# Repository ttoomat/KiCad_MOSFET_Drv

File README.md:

# Плата драйвера  MOSFET

В этой репозитории я храню печатные платы. Здесь есть одиночная печатная плата драйвера с мосфетом, будет добавлена плата полумоста на ключах
переменного тока. И общая плата, состоящая из полумостов.

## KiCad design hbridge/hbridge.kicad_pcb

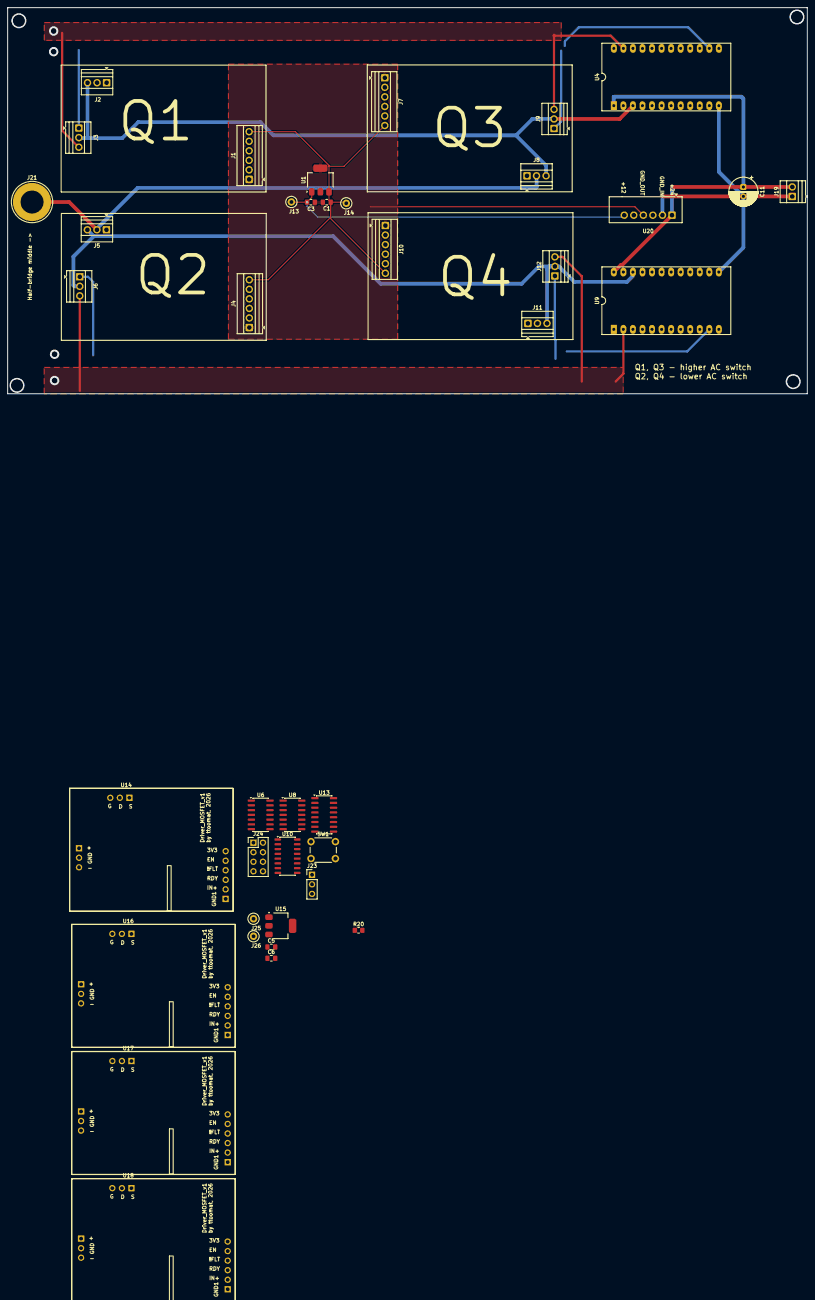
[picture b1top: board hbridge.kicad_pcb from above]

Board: 2 copper layers, 212.8 x 102.7 mm, 40 parts (0 on the bottom side), 41 nets.

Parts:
C1, C3: C; C_0805_2012Metric_Pad1.18x1.45mm_HandSolder
C5: 10u; C_0805_2012Metric_Pad1.18x1.45mm_HandSolder
C6: 2.2u; C_0805_2012Metric_Pad1.18x1.45mm_HandSolder
C11: 100-220uF/50V; CP_Radial_D7.5mm_P2.50mm
J1, J4, J7, J10: From_MCU; TerminalBlock_Xinya_XY308-2.54-6P_1x06_P2.54mm_Horizontal
J2, J5, J8, J11: MOSFET_out; TerminalBlock_Xinya_XY308-2.54-3P_1x03_P2.54mm_Horizontal
J3, J6, J9, J12: Conn_01x03; TerminalBlock_Xinya_XY308-2.54-3P_1x03_P2.54mm_Horizontal
J13, J14, J25, J26: Conn_01x01_Socket; TestPoint_Loop_D1.80mm_Drill1.0mm_Beaded
J19: 24V; TerminalBlock_Xinya_XY308-2.54-2P_1x02_P2.54mm_Horizontal
J21: Conn_01x01_Socket; Banana_Jack_1Pin
J23: Conn_01x03; PinHeader_1x03_P2.54mm_Vertical
J24: Conn_01x08_Pin; PinHeader_2x04_P2.54mm_Vertical
R20: 1k; R_0805_2012Metric_Pad1.20x1.40mm_HandSolder
SW1: SW_Push; SW_PUSH_6mm_H4.3mm
U1, U15: LDO-3.3; SOT-223-3_TabPin2
U4, U9: AM6TW-2415DZ; DIP-24_18.0mmx34.29mm_W15.24mm_LongPads
U6: MC74HC08ADG (74HC08); SOIC-14_3.9x8.7mm_P1.27mm
U8: 74AHC04; SOIC-14_3.9x8.7mm_P1.27mm
U10: 74HC165; SO-16_3.9x9.9mm_P1.27mm
U13: CD4043B; SOIC-16_3.9x9.9mm_P1.27mm
U14, U16, U17, U18: driver_MOSFET_board; плата драйвера
U20: B2412S-2WR3; TerminalBlock_Xinya_XY308-2.54-6P_1x06_P2.54mm_Horizontal

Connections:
+3V3_DRV1: C1.1, C5.1, J1.6, J4.6, J7.6, J10.6, J14.1 (Pin_1_1), J25.1 (Pin_1_1), SW1.2, U1.3 (OUT), U6.14 (VCC), U8.14 (VCC), U10.16 (VCC), U13.5 (EN), U13.16 (VDD), U14.6 (+3V3_VCC1), U15.3 (OUT), U16.6 (+3V3_VCC1), U17.6 (+3V3_VCC1), U18.6 (+3V3_VCC1)
+12V: C3.1, C6.1, J13.1 (Pin_1_1), J26.1 (Pin_1_1), U1.1 (IN), U15.1 (IN), U20.6 (+VOUT)
+15_DRV2_H: J3.1, J9.1, U4.14 (+VOUT), U14.10 (+15_VCC2), U17.10 (+15_VCC2)
+15_DRV2_L: J6.1, J12.1, U9.11 (+VOUT), U16.10 (+15_VCC2), U18.10 (+15_VCC2)
+24V_1: C11.1, J19.2, U4.1 (+VIN), U9.24 (+VIN), U20.1 (VIN)
-15_DRV2_H: J3.3, J9.3, U4.23 (-VOUT), U14.12 (-15_VEE2), U17.12 (-15_VEE2)
-15_DRV2_L: J6.3, J12.3, U9.2 (-VOUT), U16.12 (-15_VEE2), U18.12 (-15_VEE2)
/драйверы old/drain2: J5.2, J8.2, J21.1 (Pin_1_1)
EN1: J1.5, U13.2 (Q1), U14.5 (EN)
EN2: J4.5, U13.9 (Q2), U16.5 (EN)
EN3: J7.5, U13.10 (Q3), U17.5 (EN)
EN4: J10.5, U13.1 (Q4), U18.5 (EN)
ERR_CLK: J23.3, U10.2 (CP)
ERR_CS: J23.2, U10.1 (~PL)
ERR_SERIAL_DATA: J23.1, U10.9 (Q7)
FLT1: J1.4, J24.2, U6.2, U10.12 (D1), U14.4 (!FLT)
FLT2: J4.4, J24.4, U6.5, U10.14 (D3), U16.4 (!FLT)
FLT3: J7.4, J24.6, U6.10, U10.4 (D5), U17.4 (!FLT)
FLT4: J10.4, J24.8, U6.13, U10.6 (D7), U18.4 (!FLT)
GND1: C11.2, J19.1, U4.12 (-VIN), U9.13 (-VIN), U20.2 (GND_IN)
GND_DRV1: C1.2, C3.2, C5.2, C6.2, J1.1, J4.1, J7.1, J10.1, R20.2, U1.2 (GND), U6.7 (GND), U8.7 (GND), U10.8 (GND), U10.10 (DS), U10.15 (~CE), U13.8 (VSS(GND)), U14.1 (GND1), U15.2 (GND), U16.1 (GND1), U17.1 (GND1), U18.1 (GND1), U20.4 (GND_OUT)
GND_DRV2_H: J2.3, J3.2, J8.3, J9.2, U4.3 (COM), U14.9 (source), U14.11 (GND2), U17.9 (source), U17.11 (GND2)
GND_DRV2_L: J5.3, J6.2, J11.3, J12.2, U9.22 (COM), U16.9 (source), U16.11 (GND2), U18.9 (source), U18.11 (GND2)
IN1: J1.2, U14.2 (IN+)
IN2: J4.2, U16.2 (IN+)
IN3: J7.2, U17.2 (IN+)
IN4: J10.2, U18.2 (IN+)
unnamed: U6.3, U8.1
unnamed: U6.6, U8.3
unnamed: U6.8, U8.5
unnamed: U6.11, U8.9
unnamed: U8.2, U13.3 (R1)
unnamed: R20.1, SW1.1, U13.4 (S1), U13.6 (S2), U13.12 (S3), U13.14 (S4)
unnamed: U8.4, U13.7 (R2)
unnamed: U8.6, U13.11 (R3)
unnamed: U8.8, U13.15 (R4)
unnamed: U16.8 (drain), U17.8 (drain)
RDY1: J1.3, J24.1, U6.1, U10.11 (D0), U14.3 (RDY)
RDY2: J4.3, J24.3, U6.4, U10.13 (D2), U16.3 (RDY)
RDY3: J7.3, J24.5, U6.9, U10.3 (D4), U17.3 (RDY)
RDY4: J10.3, J24.7, U6.12, U10.5 (D6), U18.3 (RDY)

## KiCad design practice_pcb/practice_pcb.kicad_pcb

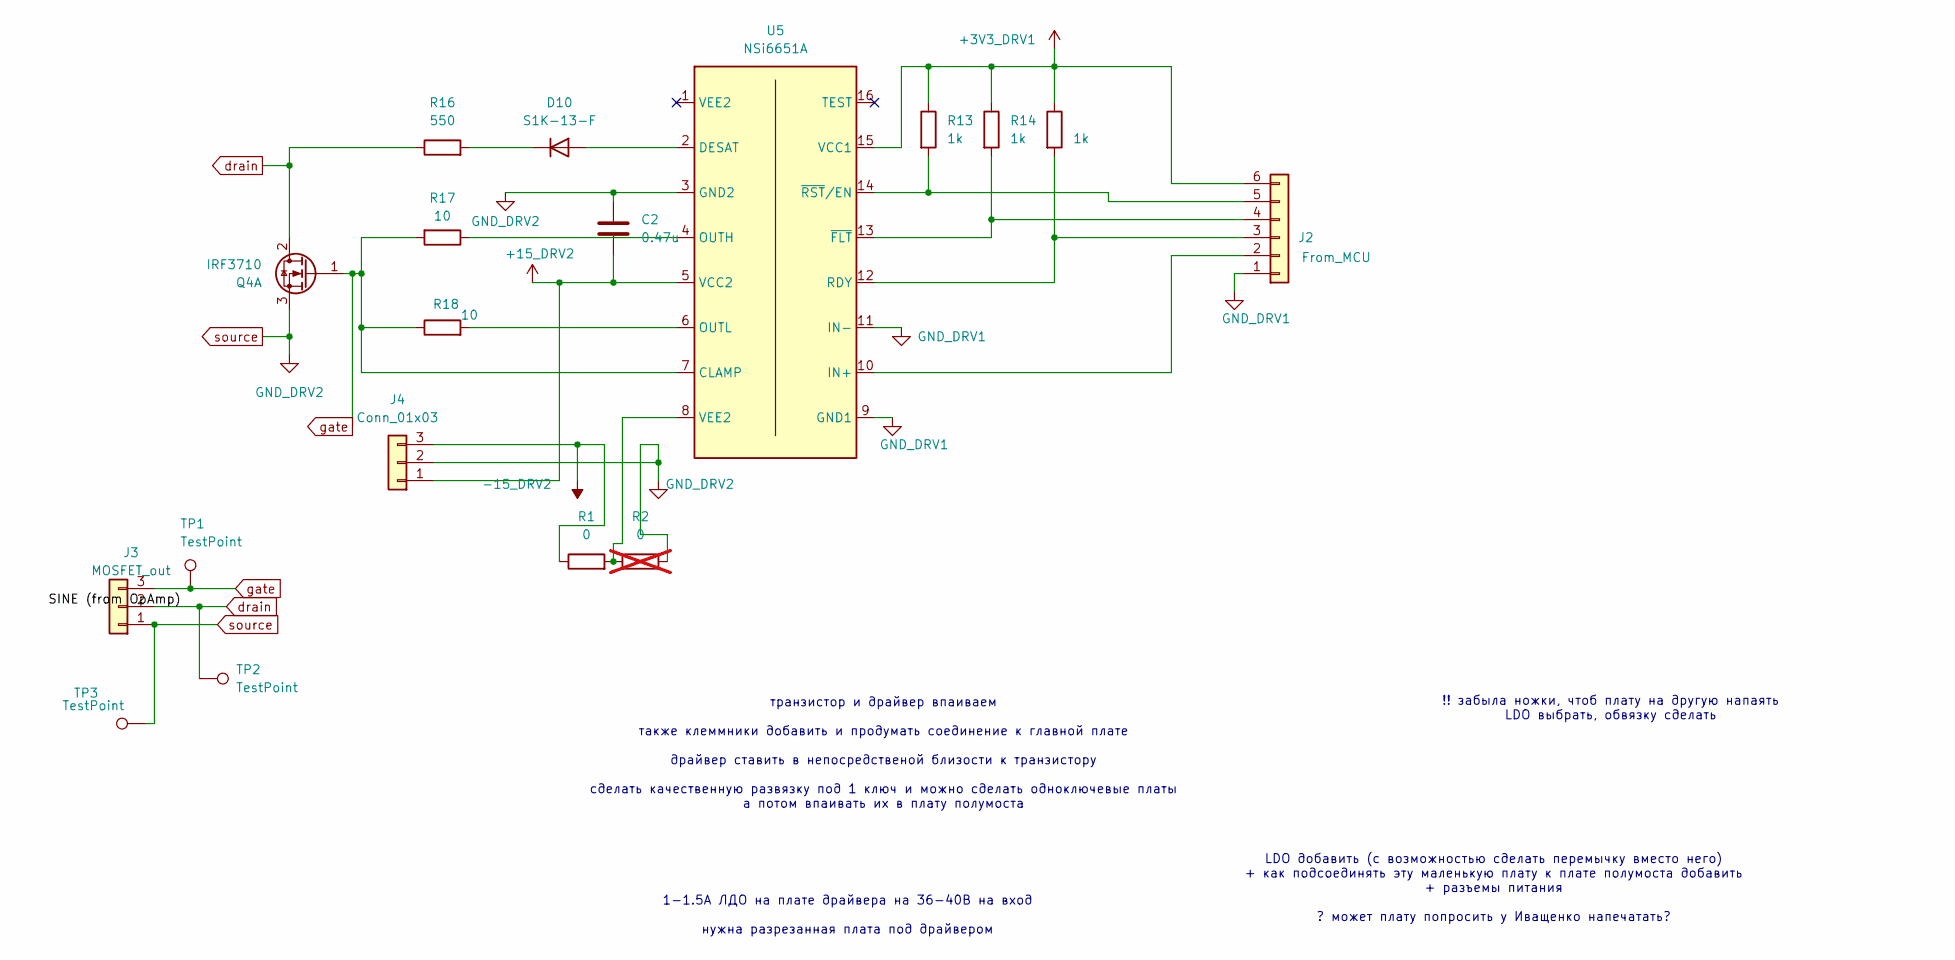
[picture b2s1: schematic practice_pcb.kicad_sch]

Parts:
C2: 0.47u; C_0805_2012Metric_Pad1.18x1.45mm_HandSolder
D10: S1K-13-F; D_SMA
J2: From_MCU; PinHeader_1x06_P2.54mm_Vertical
J3: MOSFET_out; PinHeader_1x03_P2.54mm_Vertical
J4: Conn_01x03; PinHeader_1x03_P2.54mm_Vertical
Q4: IRF3710; TO-220-3_Vertical
R1: 0; R_0805_2012Metric_Pad1.20x1.40mm_HandSolder
R2: 0; R_0805_2012Metric_Pad1.20x1.40mm_HandSolder; not fitted
R13, R14, R15: 1k; R_0805_2012Metric_Pad1.20x1.40mm_HandSolder
R16: 550; R_2512_6332Metric_Pad1.40x3.35mm_HandSolder
R17, R18: 10; R_2512_6332Metric_Pad1.40x3.35mm_HandSolder
TP1, TP2, TP3: TestPoint; TestPoint_Loop_D2.50mm_Drill1.0mm
U5: NSi6651A; SOIC-16W_7.5x10.3mm_P1.27mm

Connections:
+3V3_DRV1: J2.6, R13.1, R14.1, R15.1, U5.15 (VCC1)
+15_DRV2: C2.2, J4.1, U5.5 (VCC2)
-15_DRV2: J4.3, R1.1
GND_DRV1: J2.1, U5.9 (GND1), U5.11 (IN-)
unnamed: D10.2 (A), U5.2 (DESAT)
unnamed: D10.1 (K), R16.2
unnamed: J2.2, U5.10 (IN+)
unnamed: J2.3, R15.2, U5.12 (RDY)
unnamed: J2.4, R14.2, U5.13 (~FLT)
unnamed: J2.5, R13.2, U5.14 (~RST/EN)
unnamed: R1.2, R2.1, U5.8 (VEE2)
unnamed: R17.1, U5.4 (OUTH)
unnamed: R18.2, U5.6 (OUTL)
drain: J3.2, Q4.2 (D), R16.1, TP2.1 (1_1)
gate: J3.3, Q4.1 (G), R17.2, R18.1, TP1.1 (1_1), U5.7 (CLAMP)
source: C2.1, J3.1, J4.2, Q4.3 (S), R2.2, TP3.1 (1_1), U5.3 (GND2)

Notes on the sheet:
транзистор и драйвер впаиваем также клеммники добавить и продумать соединение к главной плате драйвер ставить в непосредственой близости к транзистору сделать качественную развязку под 1 ключ и можно сделать одноключевые платы а потом впаивать их в плату полумоста
!! забыла ножки, чтоб плату на другую напаять LDO выбрать, обвязку сделать
1-1.5А ЛДО на плате драйвера на 36-40В на вход нужна разрезанная плата под драйвером
LDO добавить (с возможностью сделать перемычку вместо него) + как подсоединять эту маленькую плату к плате полумоста добавить + разъемы питания ? может плату попросить у Иващенко напечатать?

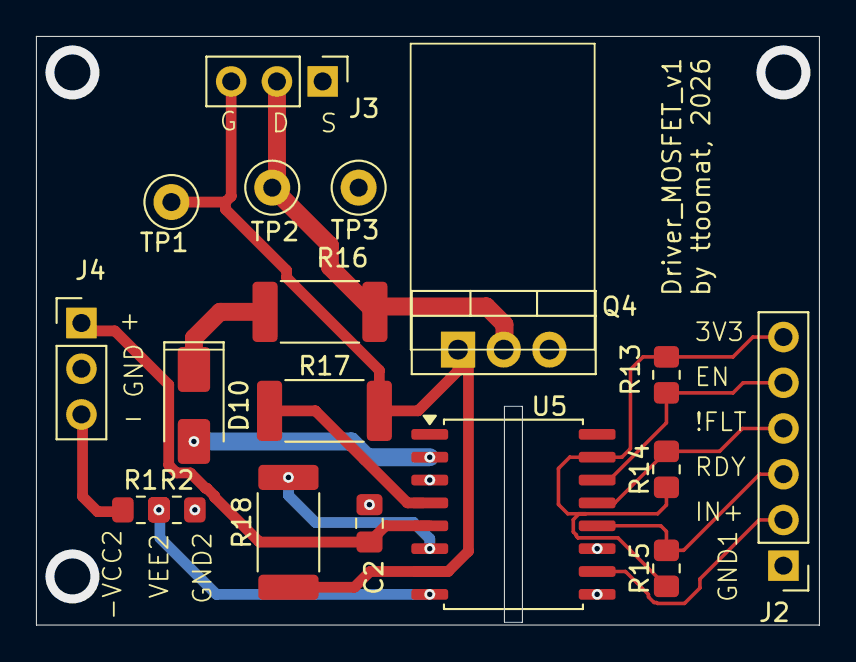
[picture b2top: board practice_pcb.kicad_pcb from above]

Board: 2 copper layers, 43.5 x 32.7 mm, 18 parts (0 on the bottom side), 16 nets.
